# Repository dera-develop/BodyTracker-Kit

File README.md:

# BODY TRACKER  
  
自作のトラッカーです．[SlimeVR](https://github.com/SlimeVR/SlimeVR-Server)を使用します．  
データの取得方法で迷走して，完成まで2か月くらいかかりました．  
ドリフトの時間サイクルは体感30分程度です．  

## 概要  
**LSM6DSV16X** のSFLPで出力されたクオータニオンを **ESP32-WROOM-32E** でI2C経由で拾ってSlimeVRに送信します．  

このトラッカーはマスターとスレーブの2個セットで製作されており，このセンサーを複数セット製作し接続することで，トラッキング箇所を自由に増やすことができます．  

詳細の仕様についてのドキュメントは[こちら](docs/overview.md)をご覧ください．  
製作手順については[こちら](docs/setup.md)をご覧ください．  

## 免責
本プロジェクトは以下の外部ソフトウェア・環境を利用しています．  
本リポジトリ内に同包はしていません．  
  
- SlimeVR Server  
[SlimeVR Server リポジトリ](https://github.com/SlimeVR/SlimeVR-Server)  
*本プロジェクトはSlimeVRのシステムと互換性を持つよう設計されていますが，SlimeVRチームによって作成，提供，または承認されたものではありません．*  
*「SlimeVR」は，SlimeVR BVの商標または登録商標です．*  
  
- Arduino  
[Arduino.cc](https://www.arduino.cc/)  
*本プロジェクトはArduino環境を利用していますが，Arduino公式プロジェクトとは無関係です．*  
*「Arduino(R)」は，Arduino Srlの商標または登録商標です．*

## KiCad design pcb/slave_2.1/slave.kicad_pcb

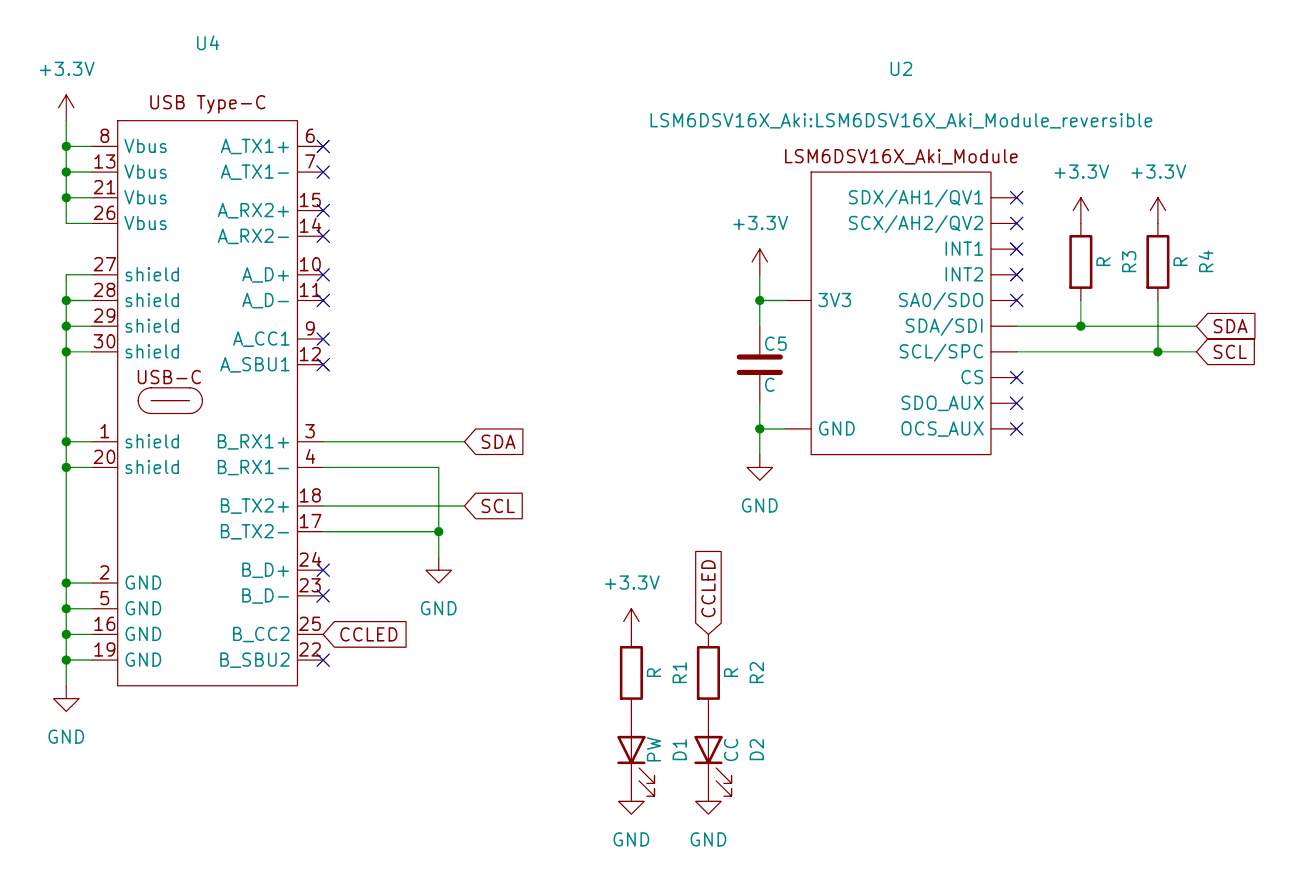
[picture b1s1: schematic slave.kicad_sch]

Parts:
C5: C; C_Disc_D3.0mm_W2.0mm_P2.50mm
D1: PW; LED_D3.0mm_Clear
D2: CC; LED_D3.0mm_Clear
R1, R2, R3, R4: R; R_Axial_DIN0207_L6.3mm_D2.5mm_P7.62mm_Horizontal
U2: LSM6DSV16X_Aki_Module_reversible
U4: JDC3-611479

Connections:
+3.3V: C5.1, R1.1, R3.1, R4.1, U2.6 (3V3), U4.8 (Vbus), U4.13 (Vbus), U4.21 (Vbus), U4.26 (Vbus)
CCLED: R2.1, U4.25 (B_CC2)
GND: C5.2, D1.1 (K), D2.1 (K), U2.5 (GND), U4.1 (shield), U4.2 (GND), U4.4 (B_RX1-), U4.5 (GND), U4.16 (GND), U4.17 (B_TX2-), U4.19 (GND), U4.20 (shield), U4.27 (shield), U4.28 (shield), U4.29 (shield), U4.30 (shield)
unnamed: D1.2 (A), R1.2
unnamed: D2.2 (A), R2.2
SCL: R4.2, U2.9 (SCL/SPC), U4.18 (B_TX2+)
SDA: R3.2, U2.8 (SDA/SDI), U4.3 (B_RX1+)

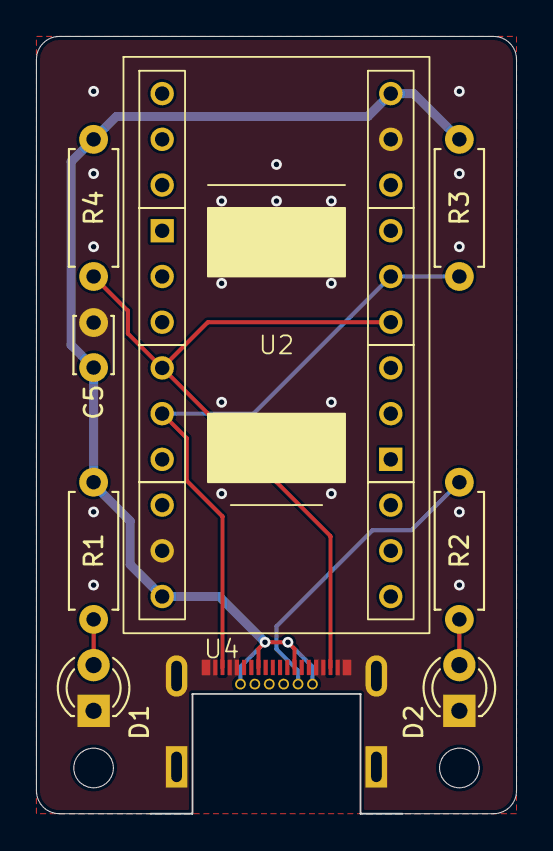
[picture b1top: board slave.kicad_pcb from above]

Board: 2 copper layers, 26.7 x 43.2 mm, 9 parts (0 on the bottom side), 7 nets.

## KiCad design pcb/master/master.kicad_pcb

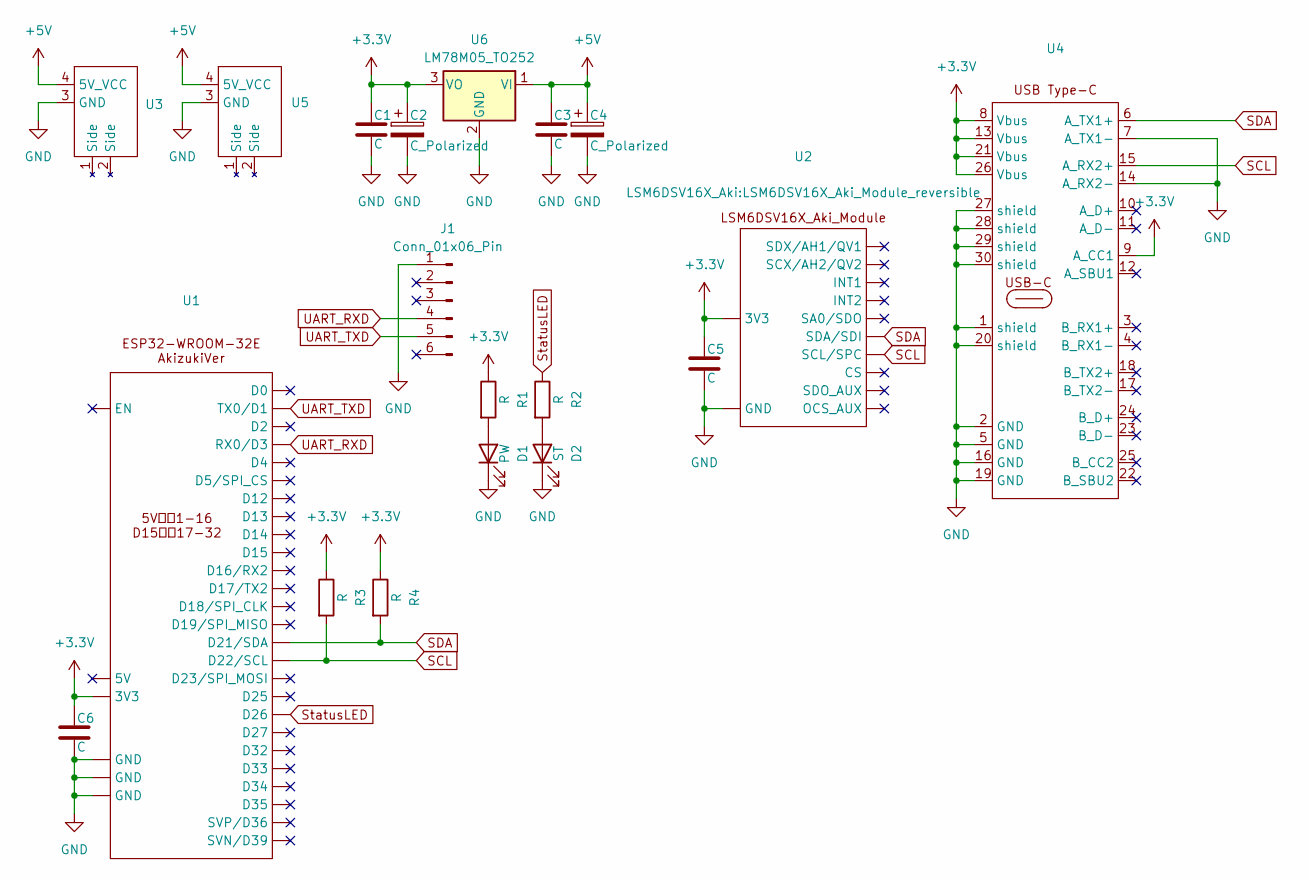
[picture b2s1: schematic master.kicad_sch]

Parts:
C1, C3, C5, C6: C; C_Disc_D3.0mm_W2.0mm_P2.50mm
C2, C4: C_Polarized; CP_Radial_D5.0mm_P2.00mm
D1: PW; LED_D3.0mm_Clear
D2: ST; LED_D3.0mm_Clear
J1: Conn_01x06_Pin; PinHeader_1x06_P2.54mm_Horizontal
R1, R2, R3, R4: R; R_Axial_DIN0207_L6.3mm_D2.5mm_P7.62mm_Horizontal
U1: ESP32-WROOM-32E_Aki
U2: LSM6DSV16X_Aki_Module_reversible
U3, U5: USB-TypeC_PowerOnly
U4: JDC3-611479
U6: LM78M05_TO252; TO-252-2

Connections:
+3.3V: C1.1, C2.1, C5.1, C6.1, R1.1, R3.1, R4.1, U1.16 (3V3), U2.6 (3V3), U4.8 (Vbus), U4.9 (A_CC1), U4.13 (Vbus), U4.21 (Vbus), U4.26 (Vbus), U6.3 (VO)
+5V: C3.1, C4.1, U3.4 (5V_VCC), U5.4 (5V_VCC), U6.1 (VI)
GND: C1.2, C2.2, C3.2, C4.2, C5.2, C6.2, D1.1 (K), D2.1 (K), J1.1, U1.3 (GND), U1.26 (GND), U1.32 (GND), U2.5 (GND), U3.3 (GND), U4.1 (shield), U4.2 (GND), U4.5 (GND), U4.7 (A_TX1-), U4.14 (A_RX2-), U4.16 (GND), U4.19 (GND), U4.20 (shield), U4.27 (shield), U4.28 (shield), U4.29 (shield), U4.30 (shield), U5.3 (GND), U6.2 (GND)
unnamed: D1.2 (A), R1.2
unnamed: D2.2 (A), R2.2
SCL: R3.2, U1.30 (D22/SCL), U2.9 (SCL/SPC), U4.15 (A_RX2+)
SDA: R4.2, U1.27 (D21/SDA), U2.8 (SDA/SDI), U4.6 (A_TX1+)
StatusLED: R2.1, U1.7 (D26)
UART_RXD: J1.4, U1.28 (RX0/D3)
UART_TXD: J1.5, U1.29 (TX0/D1)

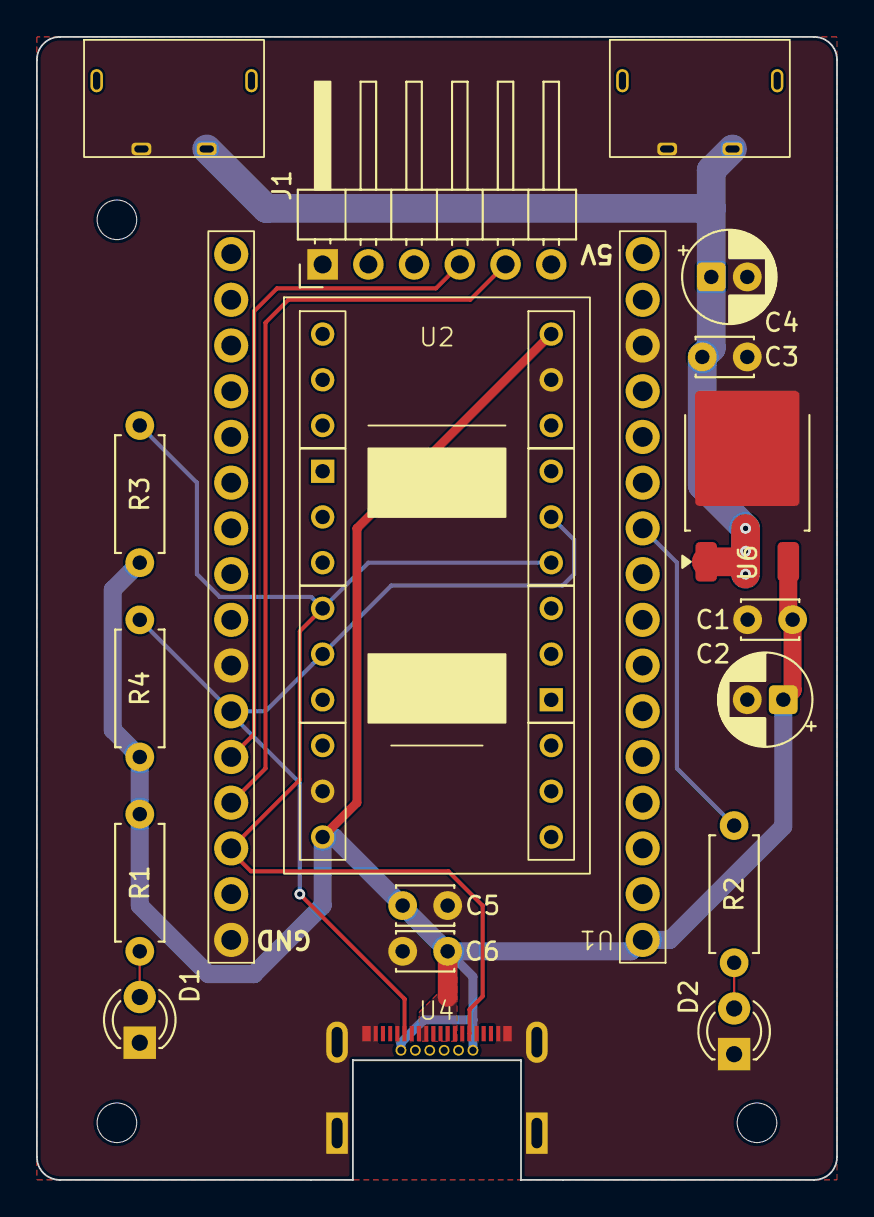
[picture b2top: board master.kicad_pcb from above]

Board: 2 copper layers, 44.5 x 63.5 mm, 19 parts (0 on the bottom side), 10 nets.
